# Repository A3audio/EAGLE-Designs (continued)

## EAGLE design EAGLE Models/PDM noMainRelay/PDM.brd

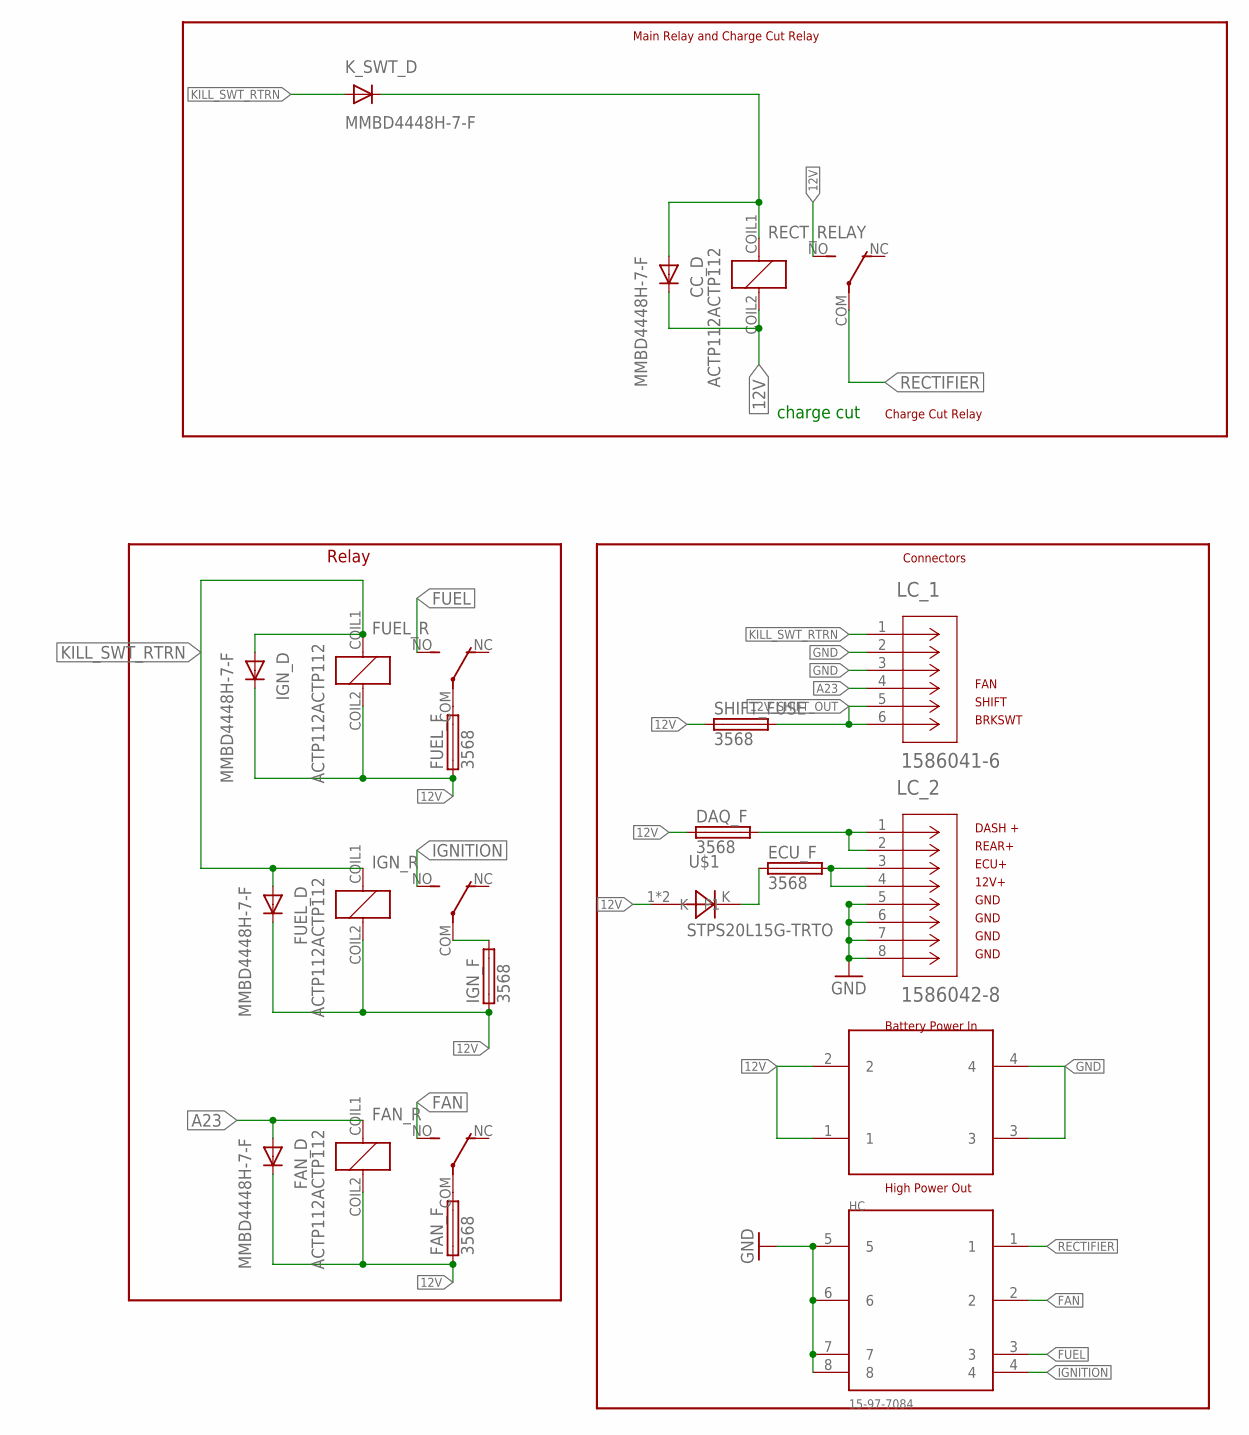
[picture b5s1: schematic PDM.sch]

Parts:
BAT_SUP: 15-97-8043
CC_D: MMBD4448H-7-F; SOT23-3
DAQ_F: 3568
ECU_F: 3568
FAN_D: MMBD4448H-7-F; SOT23-3
FAN_F: 3568
FAN_R: ACTP112ACTP112; ACTP112
FUEL_D: MMBD4448H-7-F; SOT23-3
FUEL_F: 3568
FUEL_R: ACTP112ACTP112; ACTP112
HC: 15-97-7084
IGN_D: MMBD4448H-7-F; SOT23-3
IGN_F: 3568
IGN_R: ACTP112ACTP112; ACTP112
K_SWT_D: MMBD4448H-7-F; SOT23-3
LC_1: 1586041-6
LC_2: 1586042-8
RECT_RELAY: ACTP112ACTP112; ACTP112
SHIFT_FUSE: 3568
U$1: STPS20L15G-TRTO; TO-262DIODE

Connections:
12V: BAT_SUP.1, BAT_SUP.2, CC_D.3 (C), DAQ_F.1, DAQ_F.2 (1), FAN_D.3 (C), FAN_F.1, FAN_F.2 (1), FAN_R.COIL2, FUEL_D.3 (C), FUEL_F.1, FUEL_F.2 (1), FUEL_R.COIL2, IGN_D.3 (C), IGN_F.1, IGN_F.2 (1), IGN_R.COIL2, RECT_RELAY.COIL2, RECT_RELAY.NO, SHIFT_FUSE.1, SHIFT_FUSE.2 (1), U$1.1, U$1.2 (P1)
12V_DAQ_OUT: DAQ_F.3 (2), DAQ_F.4 (2), LC_2.1, LC_2.2
12V_FUSED_ECU: ECU_F.3 (2), ECU_F.4 (2), LC_2.3, LC_2.4
12V_SHIFT_OUT: LC_1.5, LC_1.6, SHIFT_FUSE.3 (2), SHIFT_FUSE.4 (2)
A23: FAN_D.1 (A), FAN_R.COIL1, LC_1.4
ECU_PROTECTED: ECU_F.1, ECU_F.2 (1), U$1.K
FAN: FAN_R.NO, HC.2
FAN_12V: FAN_F.3 (2), FAN_F.4 (2), FAN_R.COM
FUEL: FUEL_R.NO, HC.3
FUEL_12V: FUEL_F.3 (2), FUEL_F.4 (2), FUEL_R.COM
GND: BAT_SUP.3, BAT_SUP.4, HC.5, HC.6, HC.7, HC.8, LC_1.2, LC_1.3, LC_2.5, LC_2.6, LC_2.7, LC_2.8
IGNITION: HC.4, IGN_R.NO
IGN_12V: IGN_F.3 (2), IGN_F.4 (2), IGN_R.COM
KILL_SWITCH_DIODE: CC_D.1 (A), K_SWT_D.3 (C), RECT_RELAY.COIL1
KILL_SWT_RTRN: FUEL_D.1 (A), FUEL_R.COIL1, IGN_D.1 (A), IGN_R.COIL1, K_SWT_D.1 (A), LC_1.1
RECTIFIER: HC.1, RECT_RELAY.COM

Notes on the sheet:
charge cut
Relay
DASH +
REAR+
ECU+
12V+
GND
SHIFT
BRKSWT
Charge Cut Relay
Connectors
Battery Power In
High Power Out
Main Relay and Charge Cut Relay
FAN

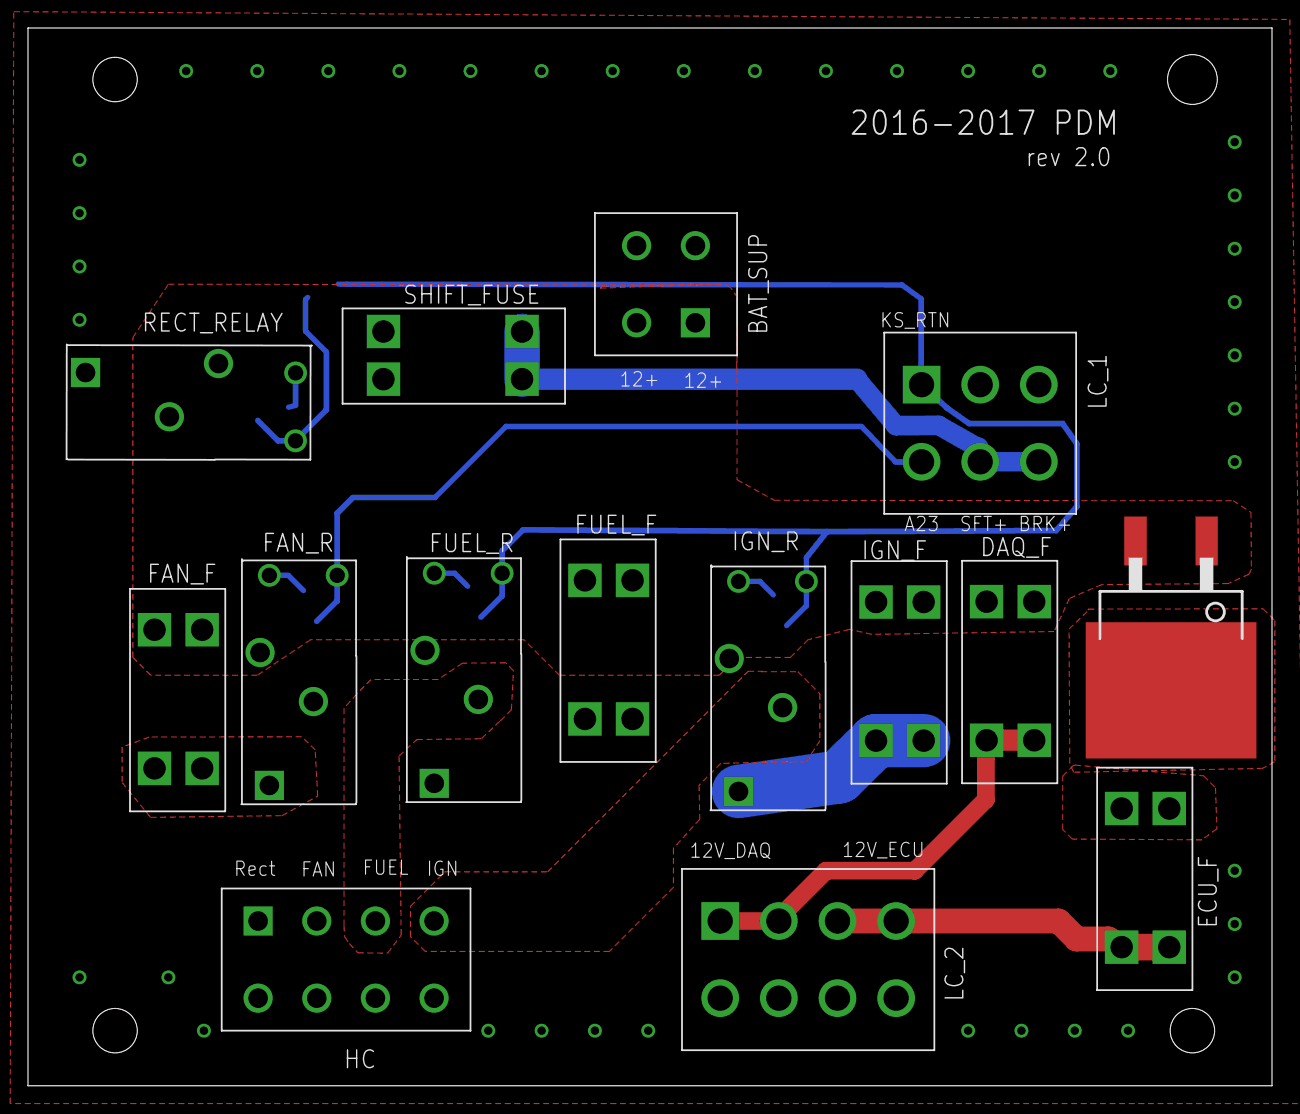
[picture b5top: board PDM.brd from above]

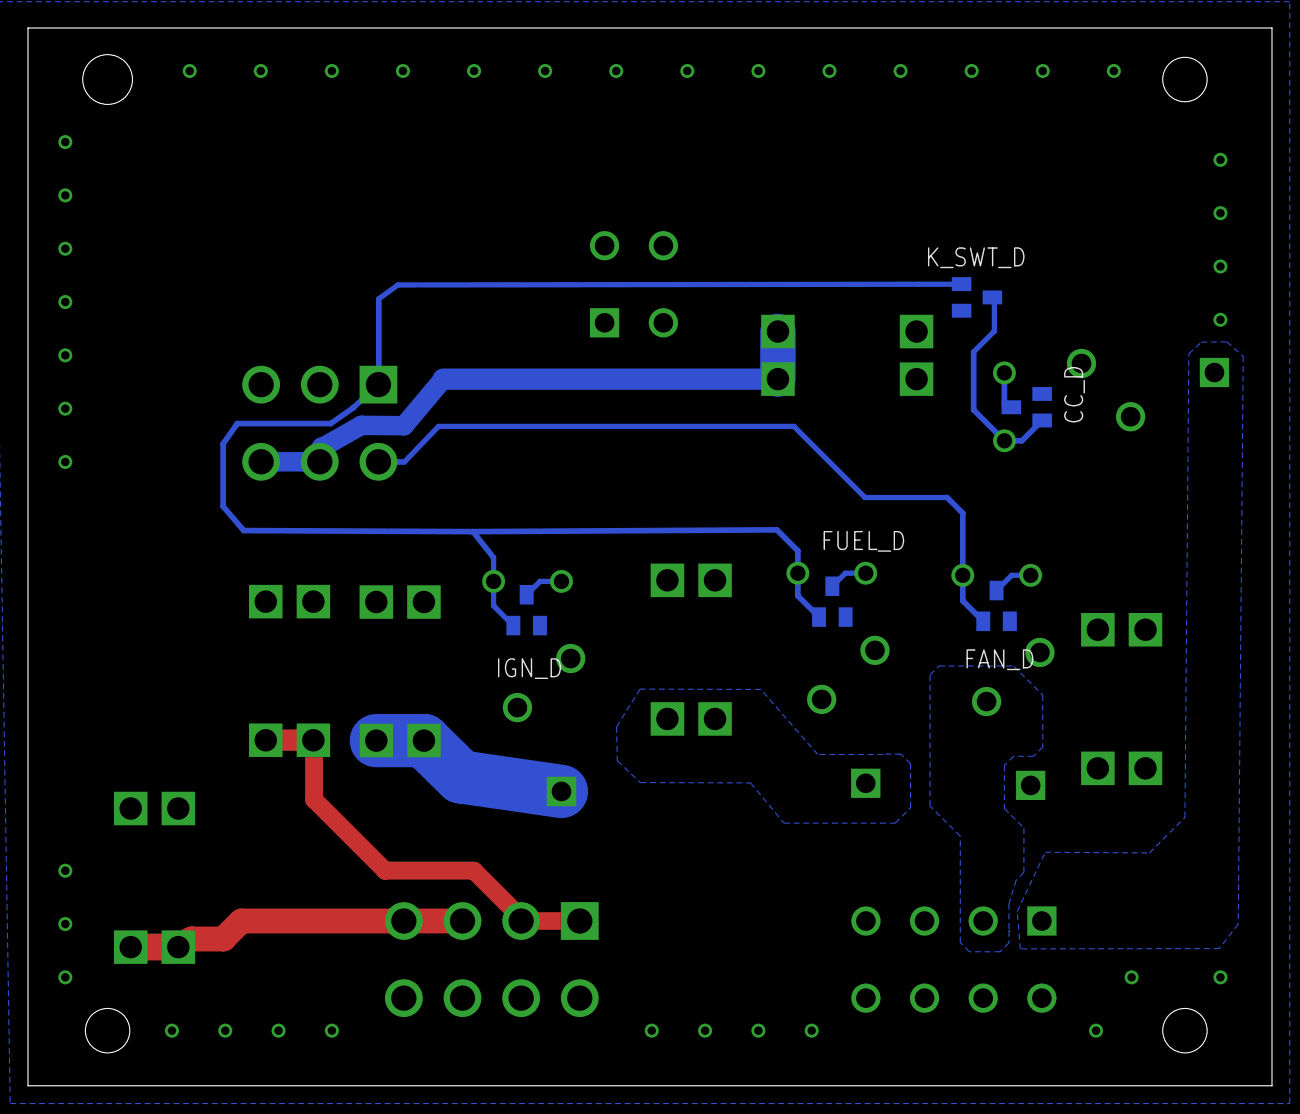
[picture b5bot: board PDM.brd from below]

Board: 2 copper layers, 88.9 x 75.6 mm, 20 parts (5 on the bottom side), 16 nets.

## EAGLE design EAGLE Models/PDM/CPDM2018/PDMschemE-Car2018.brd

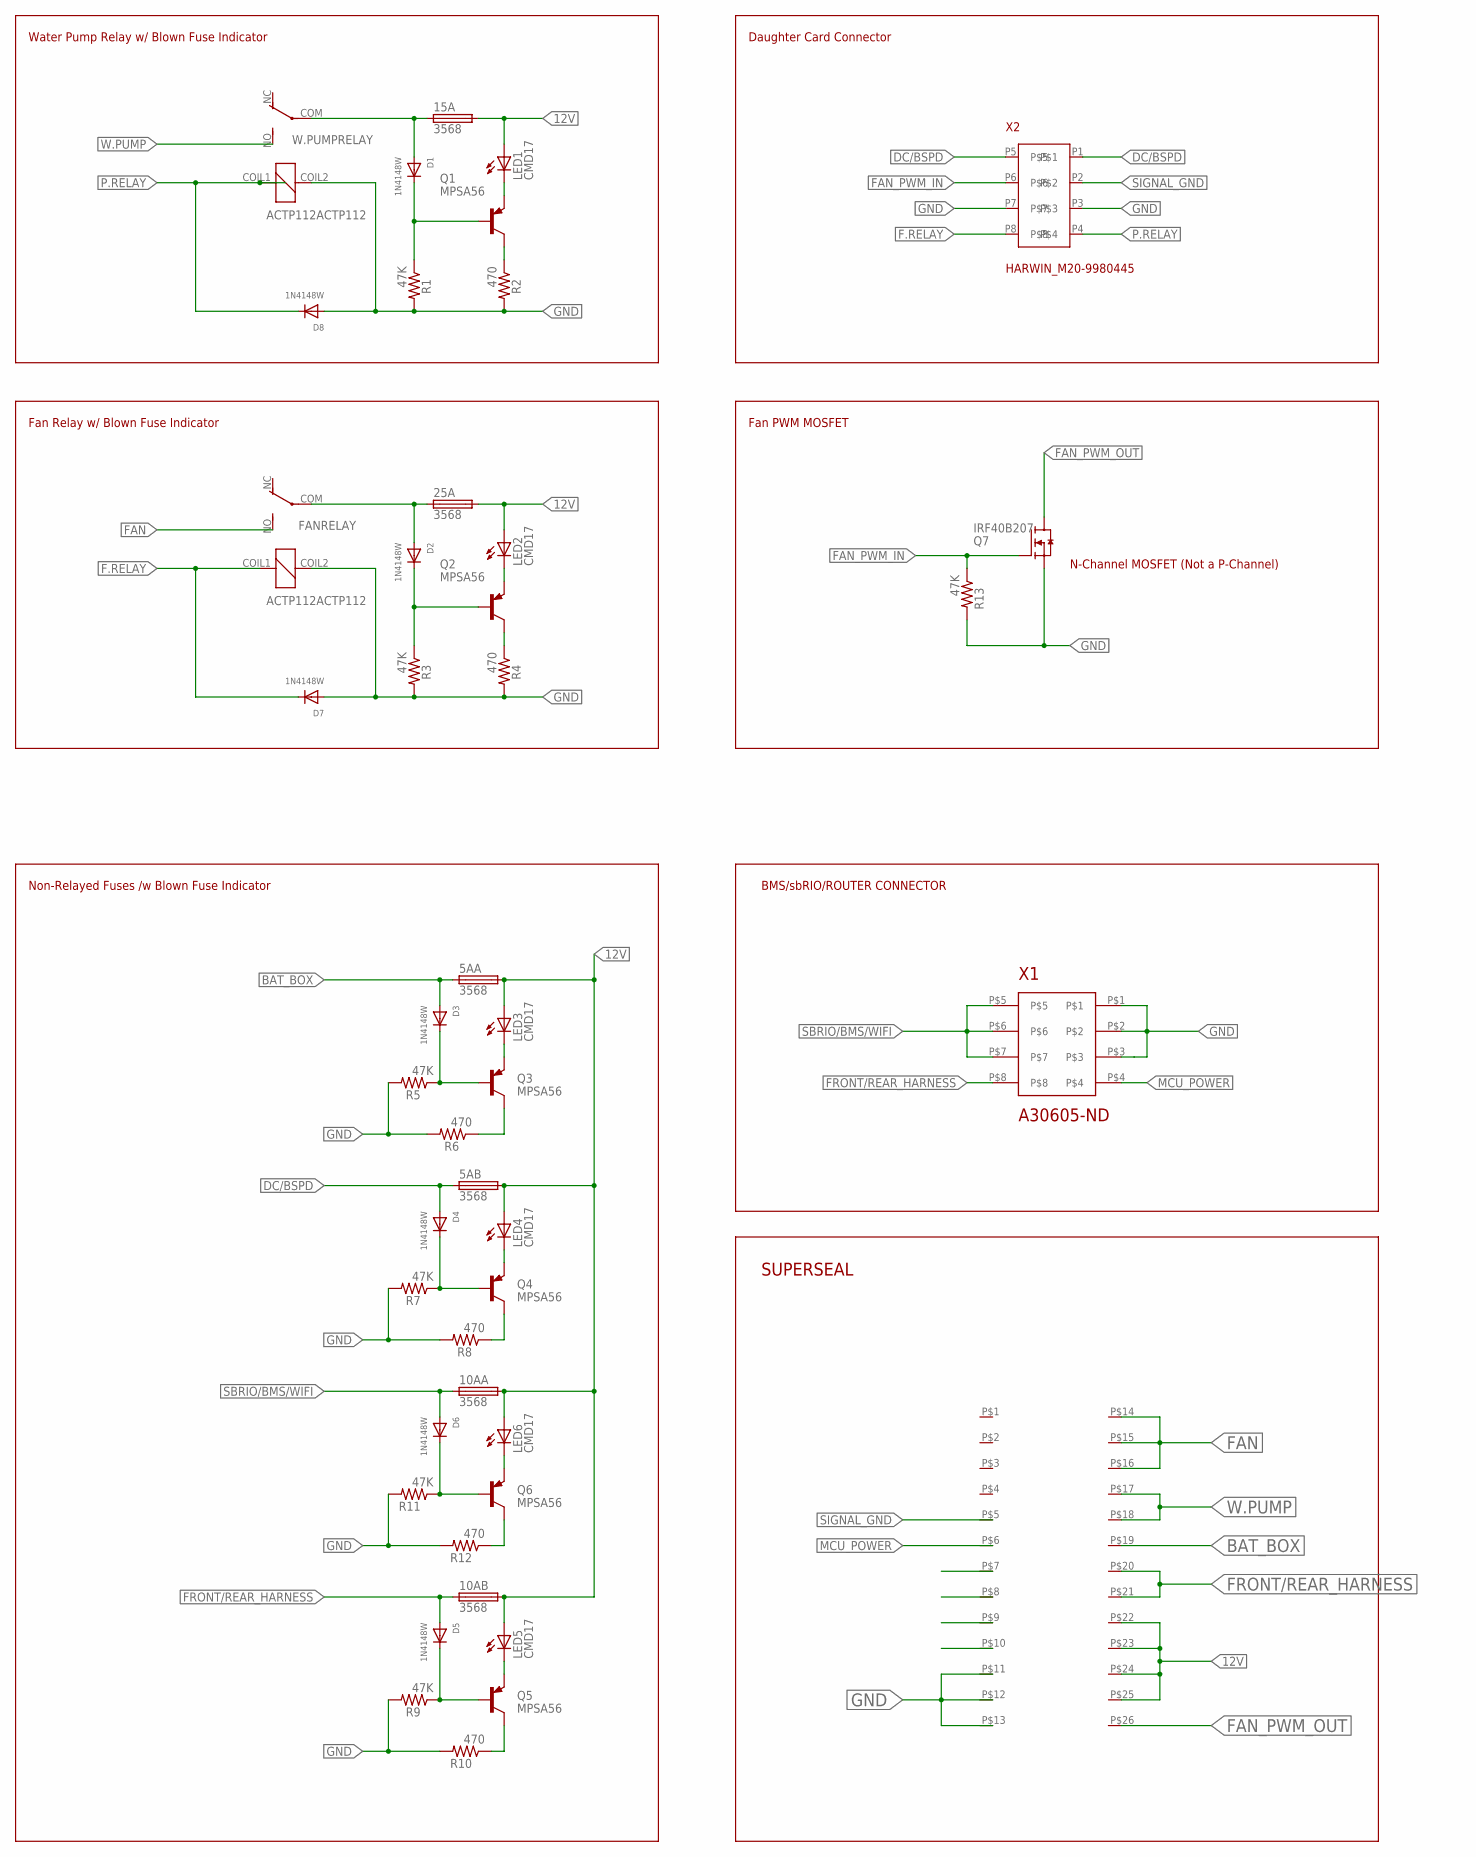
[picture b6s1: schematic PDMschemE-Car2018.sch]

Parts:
5AA, 5AB, 10AA, 10AB, 15A, 25A: 3568
D1, D2, D3, D4, D5, D6, D7, D8: 1N4148W; SOD-123
FANRELAY: ACTP112ACTP112; ACTP112
LED1, LED2, LED3, LED4, LED5, LED6: CMD17; CHIPLED_0805
Q1, Q2, Q3, Q4, Q5, Q6: MPSA56; TO92-CBE
Q7: IRF40B207; TO220-3
R1, R3, R5, R7, R9, R11, R13: 47K; R1206
R2, R4, R6, R8, R10, R12: 470; R1206
U$4: SUPERSEAL1.0_26POS_2ROW
W.PUMPRELAY: ACTP112ACTP112; ACTP112
X1: A30605-ND
X2: HARWIN_M20-9980445

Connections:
12V: 5AA.3 (2), 5AA.4 (2), 5AB.3 (2), 5AB.4 (2), 10AA.3 (2), 10AA.4 (2), 10AB.3 (2), 10AB.4 (2), 15A.3 (2), 15A.4 (2), 25A.3 (2), 25A.4 (2), LED1.A, LED2.A, LED3.A, LED4.A, LED5.A, LED6.A, U$4.P$22 (B22), U$4.P$23 (B23), U$4.P$24 (B24), U$4.P$25 (B25)
BAT_BOX: 5AA.1, 5AA.2 (1), D3.A, U$4.P$19 (B19)
DC/BSPD: 5AB.1, 5AB.2 (1), D4.A, X2.P1, X2.P5
F.RELAY: D7.C, FANRELAY.COIL1, X2.P8
FAN: FANRELAY.NO, U$4.P$14 (B14), U$4.P$15 (B15), U$4.P$16 (B16)
FAN_PWM_IN: Q7.G, R13.1, X2.P6
FAN_PWM_OUT: Q7.D, U$4.P$26 (B26)
FRONT/REAR_HARNESS: 10AB.1, 10AB.2 (1), D5.A, U$4.P$20 (B20), U$4.P$21 (B21), X1.P$8
GND: D7.A, D8.A, FANRELAY.COIL2, Q7.S, R1.2, R2.2, R3.2, R4.2, R5.2, R6.2, R7.2, R8.2, R9.2, R10.2, R11.2, R12.2, R13.2, U$4.P$11 (B11), U$4.P$12 (B12), U$4.P$13 (B13), W.PUMPRELAY.COIL2, X1.P$1, X1.P$2, X1.P$3, X2.P3, X2.P7
MCU_POWER: U$4.P$6 (B6), X1.P$4
unnamed: LED1.C, Q1.E
unnamed: Q3.C, R6.1
unnamed: LED3.C, Q3.E
unnamed: 25A.1, 25A.2 (1), D2.A, FANRELAY.COM
unnamed: Q1.C, R2.1
unnamed: D1.C, Q1.B, R1.1
unnamed: D2.C, Q2.B, R3.1
unnamed: 15A.1, 15A.2 (1), D1.A, W.PUMPRELAY.COM
unnamed: Q2.C, R4.1
unnamed: LED2.C, Q2.E
unnamed: D3.C, Q3.B, R5.1
unnamed: LED4.C, Q4.E
unnamed: D4.C, Q4.B, R7.1
unnamed: Q4.C, R8.1
unnamed: LED6.C, Q6.E
unnamed: D6.C, Q6.B, R11.1
unnamed: Q6.C, R12.1
unnamed: LED5.C, Q5.E
unnamed: D5.C, Q5.B, R9.1
unnamed: Q5.C, R10.1
P.RELAY: D8.C, W.PUMPRELAY.COIL1, X2.P4
SBRIO/BMS/WIFI: 10AA.1, 10AA.2 (1), D6.A, X1.P$5, X1.P$6, X1.P$7
SIGNAL_GND: U$4.P$5 (B5), X2.P2
W.PUMP: U$4.P$17 (B17), U$4.P$18 (B18), W.PUMPRELAY.NO

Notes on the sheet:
Water Pump Relay w/ Blown Fuse Indicator
Fan Relay w/ Blown Fuse Indicator
Non-Relayed Fuses /w Blown Fuse Indicator
Fan PWM MOSFET
N-Channel MOSFET (Not a P-Channel)
Daughter Card Connector
BMS/sbRIO/ROUTER CONNECTOR
SUPERSEAL

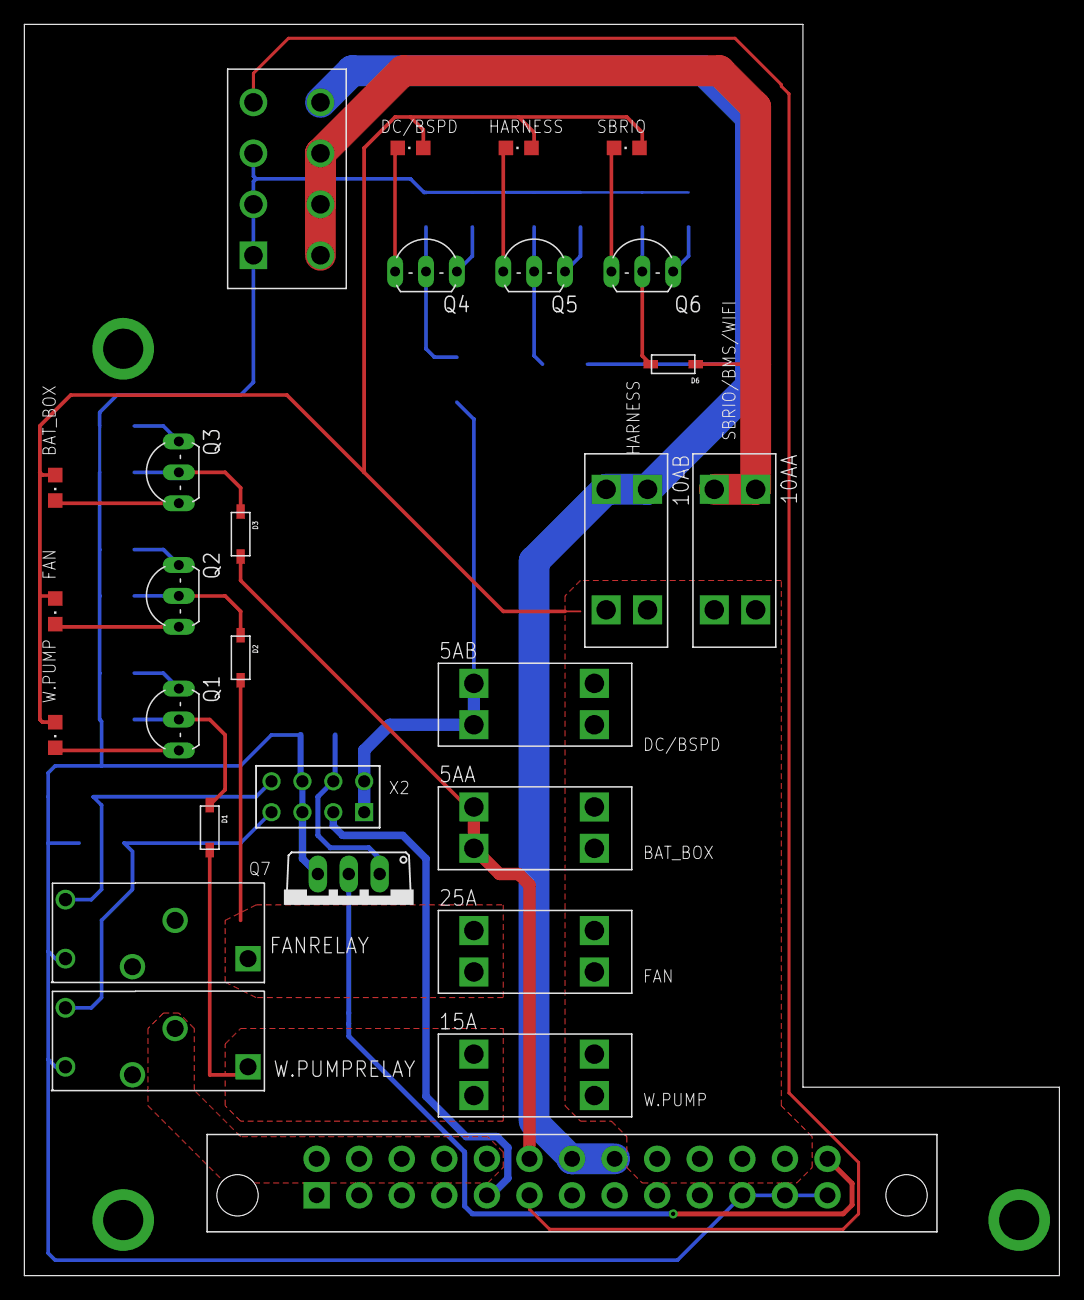
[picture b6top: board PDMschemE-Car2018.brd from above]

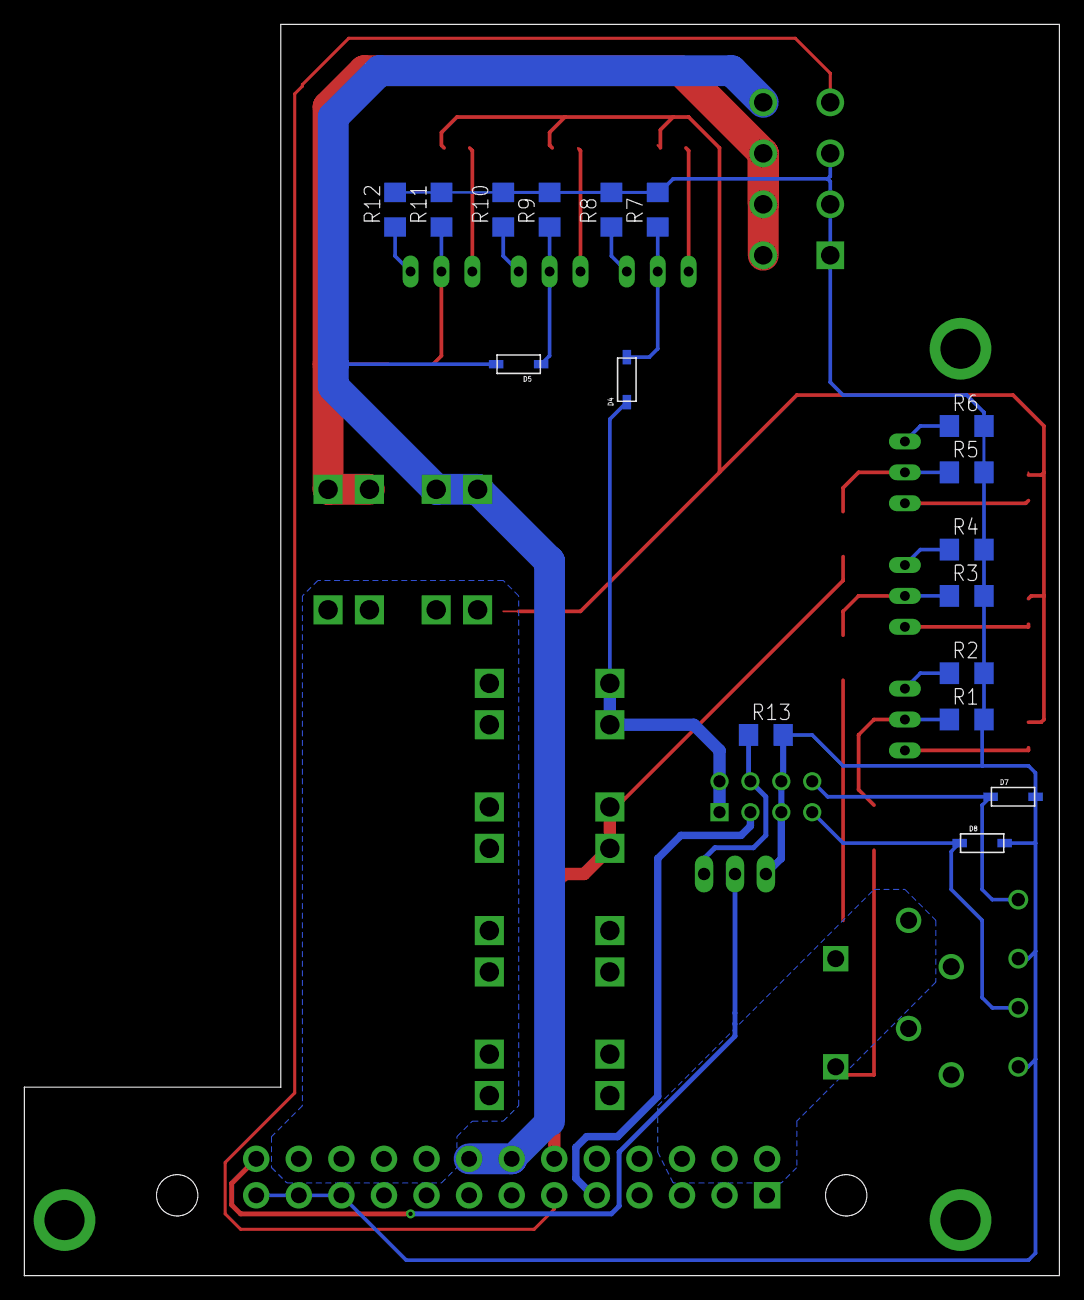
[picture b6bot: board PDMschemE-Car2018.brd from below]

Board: 2 copper layers, 85.1 x 102.9 mm, 45 parts (17 on the bottom side), 34 nets.
